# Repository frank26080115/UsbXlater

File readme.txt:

USBXLATER - Frank Zhao

Nov 11 2013:
	USB virtual COM port functionality is working, if a PS3 is not detected, then the VCP mode will be entered, and you should be able to use it to analyze some USB stuff

	passthrough mode can start but is not sending to the FS interface yet, I need to figure out why it's not working

	major improvements to debug, and HC allocation
	fixed many hardfaults
	added COM port commands

Nov 8 2013:
	please see
	http://eleccelerator.com/usbxlater-preview/
	right now this is just a rough firmware enough to play BF4

	there is some work-in-progress code that extends the functionality to include
	VCP and traffic analysis capabilities, these are untested

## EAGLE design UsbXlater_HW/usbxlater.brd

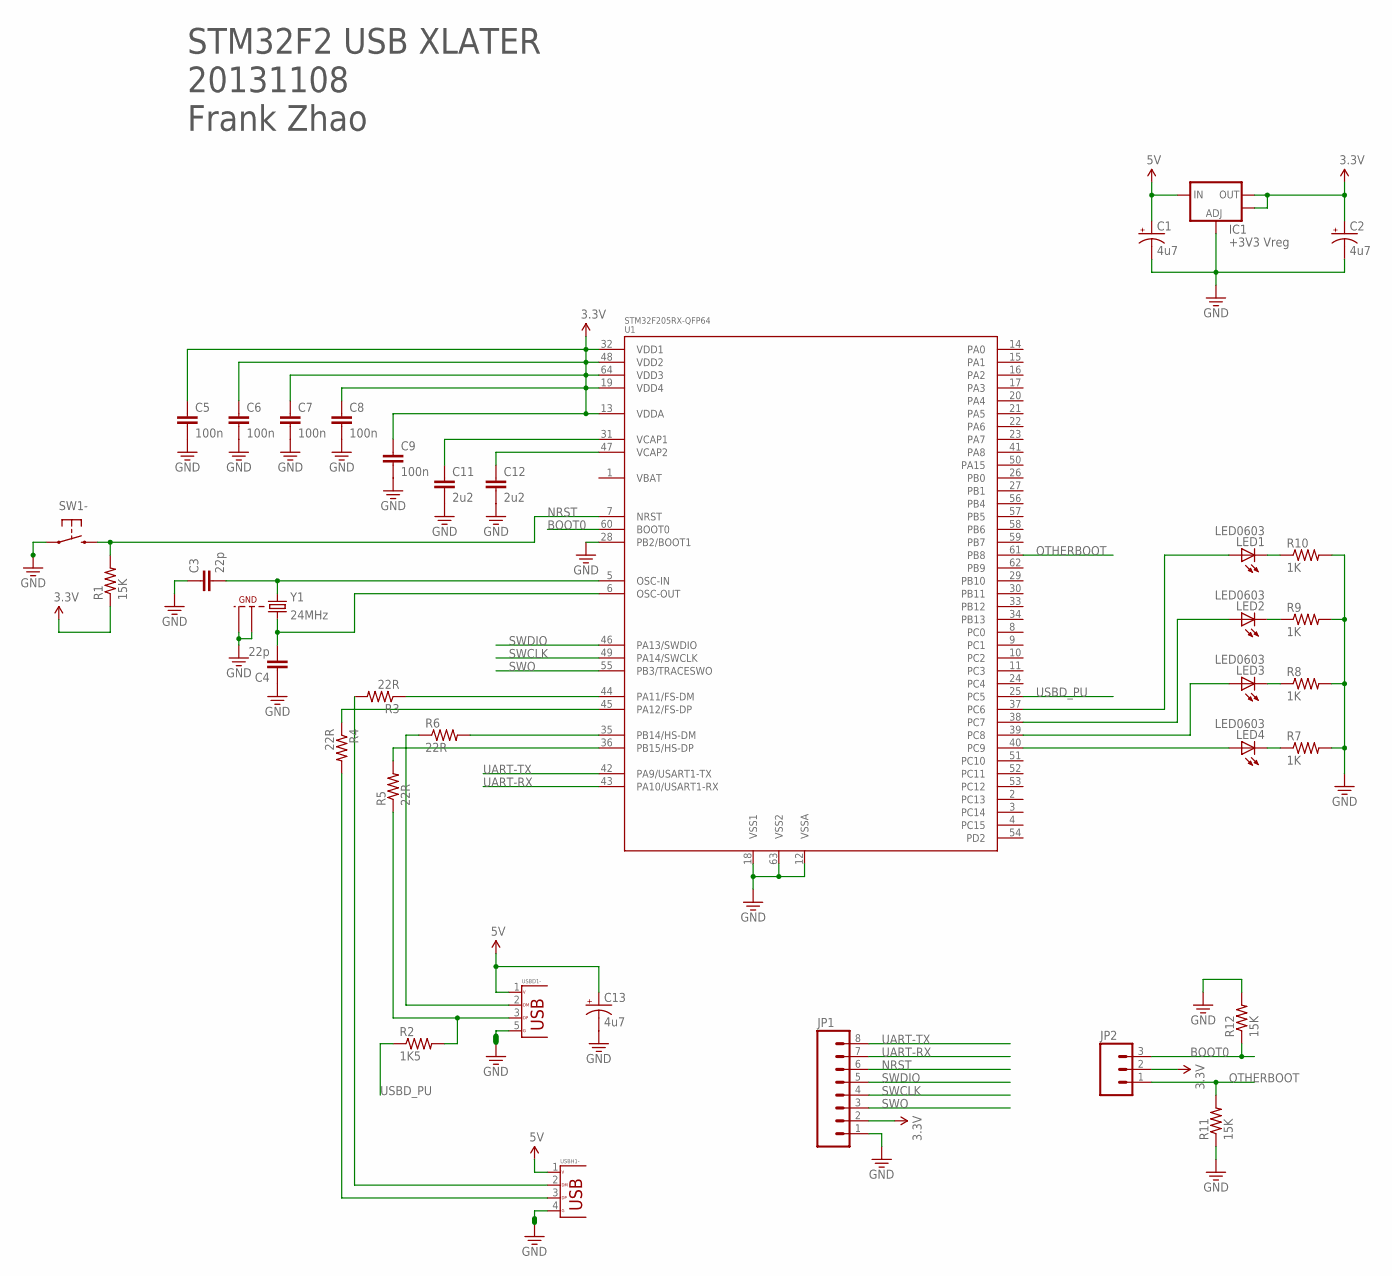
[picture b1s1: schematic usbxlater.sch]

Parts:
C1, C2, C13: 4u7; EIA3216
C3, C4: 22p; 0603-CAP-NOLEAK
C5, C6, C7, C8, C9: 100n; 0603-CAP-NOLEAK
C11, C12: 2u2; 0603-CAP-NOLEAK
IC1: +3V3 Vreg; SOT223
JP1: M081X08; 1X08
JP2: M03PTH; 1X03
LED1, LED2, LED3, LED4: LED0603; LED-0603
R1: 15K; 0603-RES
R2: 1K5; 0603-RES
R3, R4, R5, R6: 22R; 0603-RES
R7, R9: 1K; 0603-RES-NOLEAK
R8, R10: 1K; 0603-RES
R11, R12: 15K; 0603-RES-NOLEAK
SW1: SWITCH-B3U-1100-BOSS; SWITCH-TACT-B3U-1100P-B
U1: STM32F205RX-QFP64; TQFP64
USBD1: USB-6S-MICRO_B; USB_MICRO_B
USBH1: USB-A-RV
Y1: 24MHz; CRYSTAL-SMD-3.2X2.5

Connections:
3.3V: C2.A (+), C5.1, C6.1, C7.1, C8.1, C9.1, IC1.2 (OUT), IC1.4 (OUT), JP1.2, JP2.2, R1.1, U1.13 (VDDA), U1.19 (VDD4), U1.32 (VDD1), U1.48 (VDD2), U1.64 (VDD3)
5V: C1.A (+), C13.A (+), IC1.3 (IN), USBD1.1 (VBUS), USBH1.1 (VBUS)
BOOT0: JP2.3, R12.1, U1.60 (BOOT0)
GND: C1.C (-), C2.C (-), C3.1, C4.1, C5.2, C6.2, C7.2, C8.2, C9.2, C11.2, C12.2, C13.C (-), IC1.1 (ADJ), JP1.1, R7.2, R8.2, R9.2, R10.2, R11.1, R12.2, SW1.1, SW1.BOSS, U1.12 (VSSA), U1.18 (VSS1), U1.28 (PB2/BOOT1), U1.63 (VSS2), USBD1.5 (GND), USBD1.P$1, USBD1.P$2, USBD1.P$3, USBD1.P$4, USBD1.S1, USBD1.S2, USBH1.4 (GND), USBH1.S1, USBH1.S2, USBH1.S3, USBH1.S4, Y1.2 (GND1), Y1.4 (GND2)
unnamed: C3.2, U1.5 (OSC-IN), Y1.1
unnamed: LED1.C, R10.1
unnamed: R4.2, USBH1.3 (D+)
unnamed: R3.2, USBH1.2 (D-)
unnamed: LED2.C, R9.1
unnamed: C4.2, U1.6 (OSC-OUT), Y1.3 (2)
unnamed: C12.1, U1.47 (VCAP2)
unnamed: LED3.C, R8.1
unnamed: C11.1, U1.31 (VCAP1)
unnamed: LED4.C, R7.1
unnamed: LED4.A, U1.40 (PC9)
unnamed: R4.1, U1.45 (PA12/FS-DP)
unnamed: R3.1, U1.44 (PA11/FS-DM)
unnamed: LED3.A, U1.39 (PC8)
unnamed: LED2.A, U1.38 (PC7)
unnamed: LED1.A, U1.37 (PC6)
unnamed: R6.2, U1.35 (PB14/HS-DM)
unnamed: R5.2, U1.36 (PB15/HS-DP)
unnamed: R6.1, USBD1.2 (D-)
unnamed: R2.2, R5.1, USBD1.3 (D+)
NRST: JP1.6, R1.2, SW1.2, U1.7 (NRST)
OTHERBOOT: JP2.1, R11.2, U1.61 (PB8)
SWCLK: JP1.4, U1.49 (PA14/SWCLK)
SWDIO: JP1.5, U1.46 (PA13/SWDIO)
SWO: JP1.3, U1.55 (PB3/TRACESWO)
UART-RX: JP1.7, U1.43 (PA10/USART1-RX)
UART-TX: JP1.8, U1.42 (PA9/USART1-TX)
USBD_PU: R2.1, U1.25 (PC5)

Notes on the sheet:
STM32F2 USB XLATER 20131108 Frank Zhao

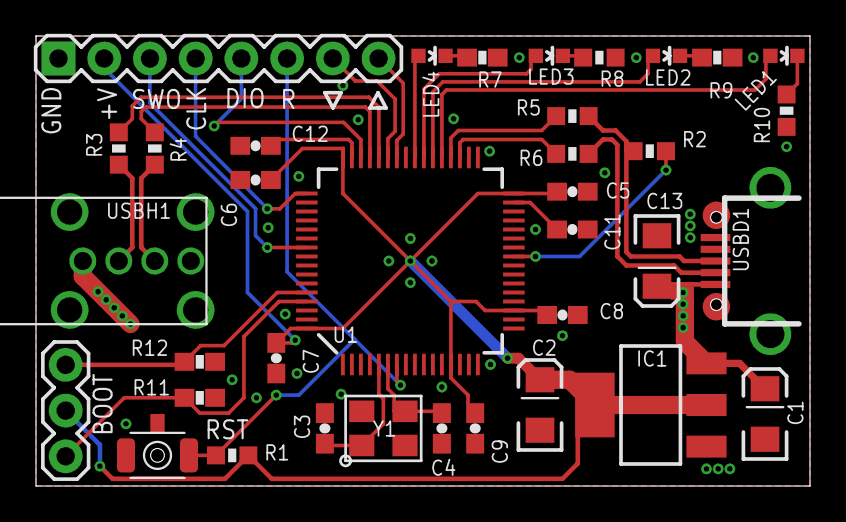
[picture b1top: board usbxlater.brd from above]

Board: 2 copper layers, 43.0 x 25.0 mm, 36 parts (0 on the bottom side), 32 nets.

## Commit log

2013-11-09 build config editted
2013-11-09 vcp working, tried to improve parser, and more...
    new startup sequencing
    better usage of external pull-up resistor
    improved system timer
2013-11-09 converted dir slashes in project config
2013-11-10 forgot to add back kbm2c to hid decoder
2013-11-10 fixed bugs, improved hc alloc, tried to make passthrough work, added cmd handler
2013-11-11 eliminated some \r\n
2013-11-11 more fixes, better vcp
2013-11-11 last commit broke things
2013-11-18 DS4 to DS3 adaption, working on config, see msg
    a lot of work done on kbm2ctrl, a lot more still left to do
    the next todo is getting everything to work on PS4
    left in some debug in hopes of hunting down a freeze situation
2013-11-19 dualshock4 emu, watchdog timer, not a clean commit
2013-11-19 DS4 SetFeature 0x14 supported, still doesn't actually respond
2013-11-22 fix for set_idle stalling
2014-01-03 added stm32f4
2014-01-12 fix for stm32f4 clock
2014-01-12 flash and crc utils
2014-01-12 final fix for crc32
2014-01-13 small fixes
2014-01-13 added bt related stuff
2014-01-13 temporary fix for babble error
2014-01-13 fixes to HCI, cmds and events now work
2014-02-06 with btstack
2014-02-09 revamped USB
2014-02-09 revamped USB new files missed in last commit
2014-02-13 improved usb reliability
2014-02-19 more usb fixes, complete BT connection from DS4
2014-02-24 bt connects ps4, fixed mixed pkt type in xpo
2014-03-02 bf4 playable
    see
    http://eleccelerator.com/keyboard-and-mouse-for-playstation-4-games-second-prototype/
